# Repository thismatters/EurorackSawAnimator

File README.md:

# Saw Animator

```
     |\
<--> | \ | <-->
        \|
```

The Saw Animator combines a signal from an LFO with a saw audio signal to produce interesting overtones. In effect the LFO modulates the frequency of the saw wave causing the waveform to dance side-to-side on the oscilloscope. This module has an LFO of its own with adjustable rate, this can be overridden with a different CV signal.

The circuit here is based on the [Yusynth Saw Animator](https://yusynth.net/Modular/EN/SAWANIM/index.html) with minor tweaks to make it more Eurorack friendly. The changes I've made are thus:
* Selected resistors appropriate for +/-12V rails,
* Added polarity protection so that a backward power header doesn't fry anything (twin series schotty diodes: BAT54SL),
* Full surface mount design.

The Yusynth page is a treasure trove of information about this circuit that I am too amateur to claim as my own; please read that outstanding page before using this circuit. The page provides many details and other implementations of this circuit that you may find suitable.

The KiCAD project here uses the library/footprints [found in my companion repo](https://github.com/thismatters/EurorackKiCAD).

## Width

10hp on an Intellijel 1U rack.

## Inputs

Single potentiometer for adjusting LFO rate. Input jack for control voltage which overrides the LFO. Input jack for saw audio signal.

## Outputs

Output jack for animated saw output. LED which tracks the internal LFO.

## Adjustment

### Refine shape

- Ground the LFO input
- Connect a balanced saw wave (+/-5V) to the input
- Connect oscilloscope to the output
- Adjust RV2 (the one in the middle layer) until the triangle looks smooth

###  Set Balance

- Adjust RV1 so that the output is blanaced in the +/-5V range.

## Vendors

There are part numbers in the [BOM](saw-animator.csv) for many of the parts (not for basic passives though) at the following vendors:

* [Mouser](https://www.mouser.com): Needs no introduction. Get your ICs from here (or [digikey](https://www.digikey.com)).
* [Tayda Electronics](https://www.taydaelectronics.com/): Good supplier for passive components; audio jacks, and potentiometers. Their audio jacks are slightly smaller than the thonkiconn from thonk.
* [Love My Switches](https://lovemyswitches.com/): Has [really good knobs](https://lovemyswitches.com/anodized-aluminum-knob-the-lo-fi-1-4-smooth-shaft-12-5mm-od/) to go on those potentiometers!
* [OSHPark](https://oshpark.com/): Fast and (relatively) cheap PCB manufacturer. [V0 PCB](https://oshpark.com/shared_projects/MXBVaxpS)

## Issues

### V0
- The output saw waveshape is slightly distorted at the bottom, the slope is a little off
- Assembly was harder than necessary because the two boards with SMD components did not have enough support tabs to keep them together; each board had to be registered for solder paste application separately.

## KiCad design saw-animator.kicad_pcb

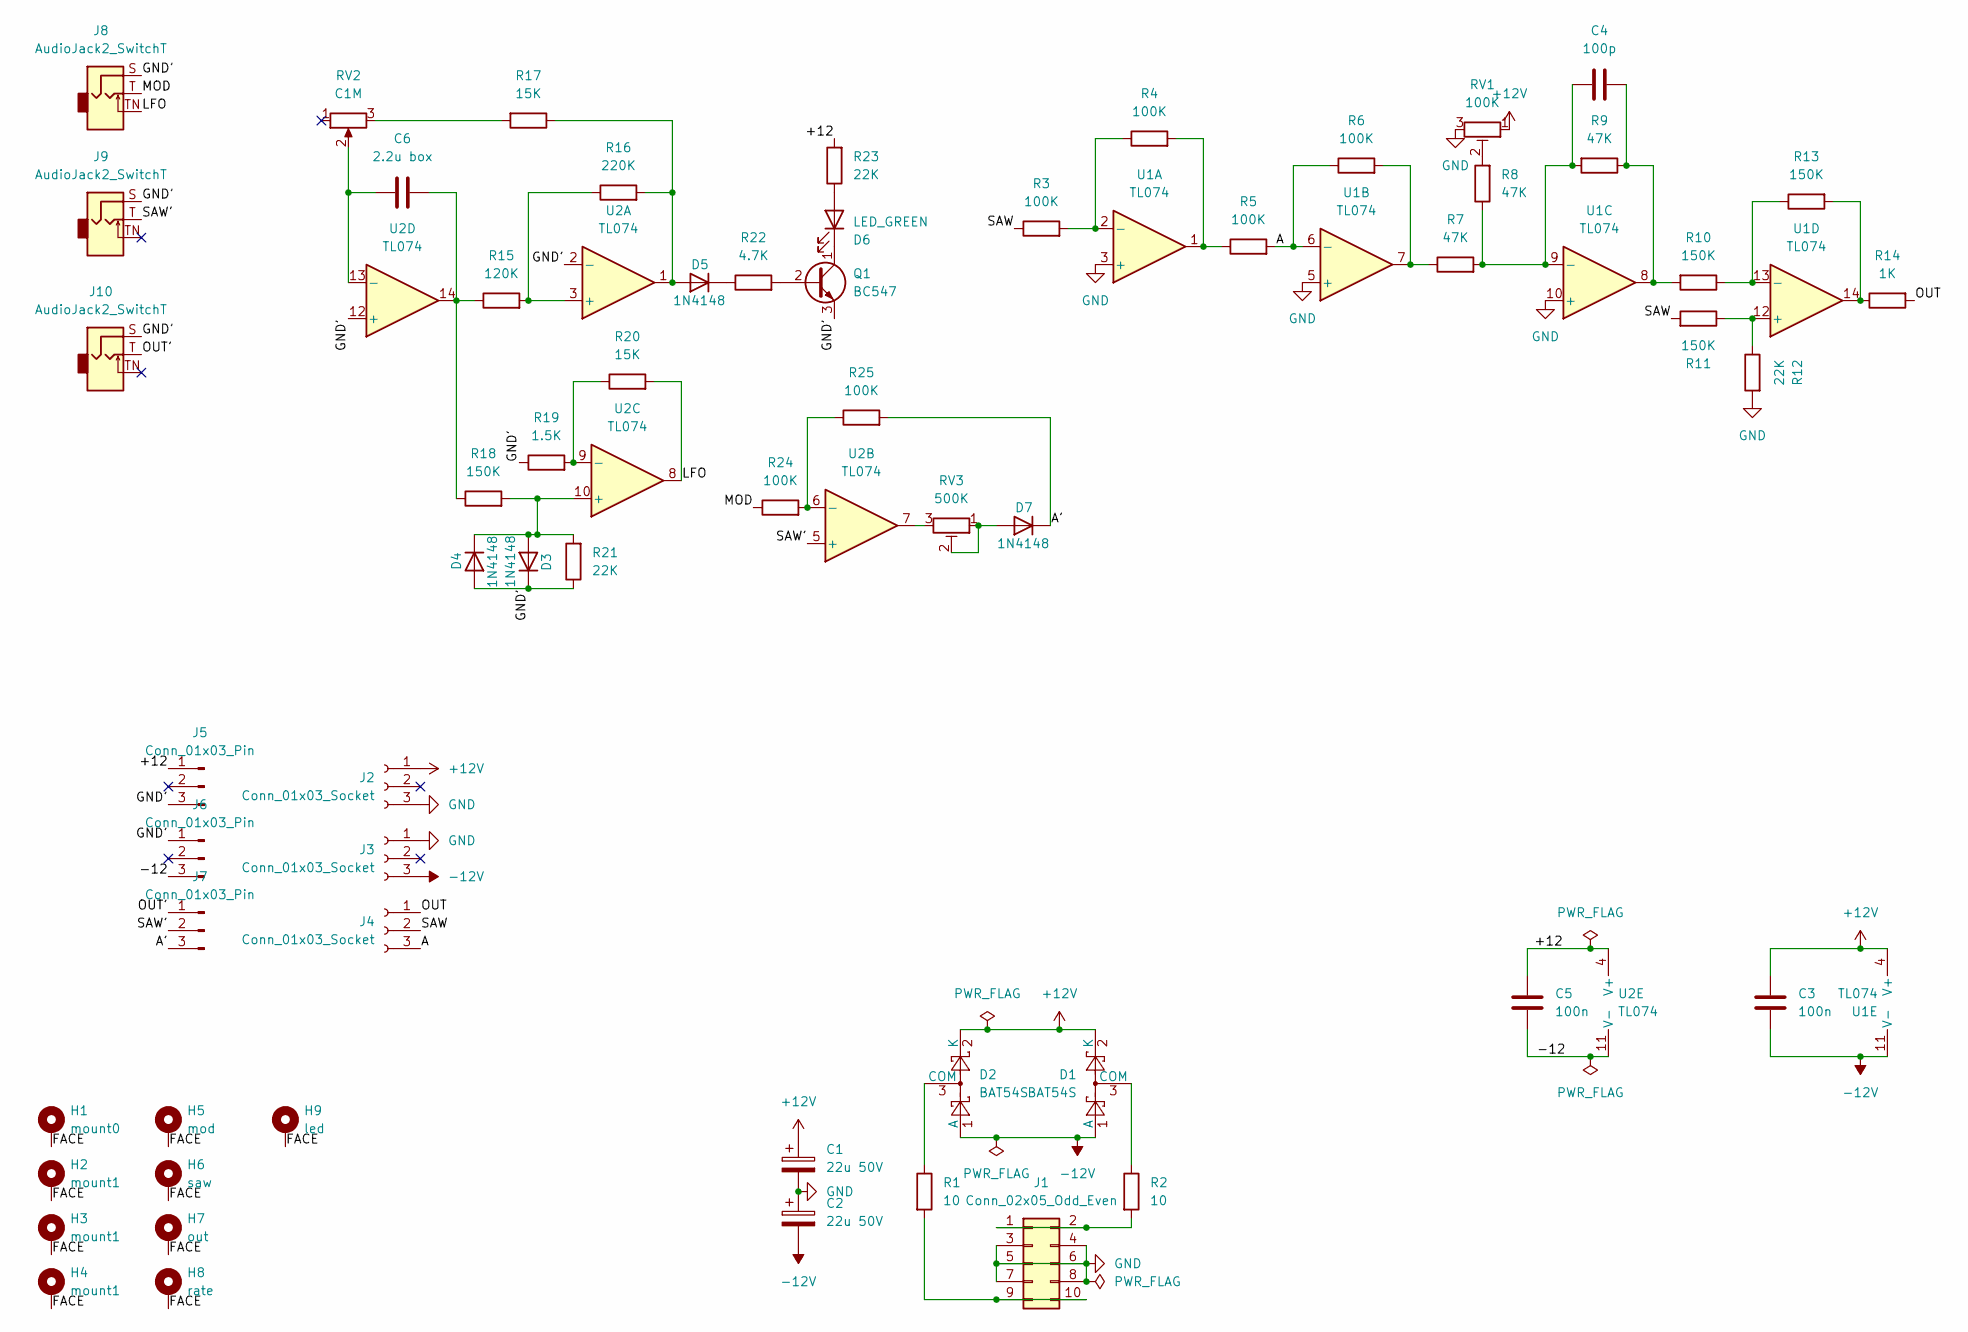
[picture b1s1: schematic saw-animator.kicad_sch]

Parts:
C1, C2: 22u 50V; CP_Radial_D5.0mm_P2.50mm
C3, C5: 100n; C_0805_2012Metric
C4: 100p; C_0805_2012Metric
C6: 2.2u box; C_Rect_L7.2mm_W7.2mm_P5.00mm_FKS2_FKP2_MKS2_MKP2
D1, D2: BAT54S; SOT-23; PartNum 863-BAT54SLT1G
D3, D4, D5, D7: 1N4148; D_SOD-323_HandSoldering
D6: LED_GREEN; LED_D3.0mm
H1: mount0; Mech-MountingHole
H2, H3, H4: mount1; Mech-MountingHole
H5: mod; Mech-AudioJack-Hole-Input-CV
H6: saw; Mech-AudioJack-Hole-Input
H7: out; Mech-AudioJack-Hole-Output
H8: rate; Mech-Potentiometer-Hole_level_90deg
H9: led; Mech-LED-Hole-3mm-Bezel
J1: Conn_02x05_Odd_Even; PinHeader_2x05_P2.54mm_Vertical; PartNum A-2939
J2, J3, J4: Conn_01x03_Socket; PinSocket_1x03_P2.54mm_Vertical
J5, J6, J7: Conn_01x03_Pin; PinHeader_1x03_P2.54mm_Vertical
J8, J9, J10: AudioJack2_SwitchT; AudioJack2_Tayda_A-2566; PartNum A-2566
Q1: BC547; TO-92_Inline_Wide; PartNum 637-BC547C
R1, R2: 10; R_0805_2012Metric
R3, R4, R5, R6, R24, R25: 100K; R_0805_2012Metric
R7, R8, R9: 47K; R_0805_2012Metric
R10, R11, R13, R18: 150K; R_0805_2012Metric
R12, R21, R23: 22K; R_0805_2012Metric
R14: 1K; R_0805_2012Metric
R15: 120K; R_0805_2012Metric
R16: 220K; R_0805_2012Metric
R17, R20: 15K; R_0805_2012Metric
R19: 1.5K; R_0805_2012Metric
R22: 4.7K; R_0805_2012Metric
RV1: 100K; Potentiometer_Bourns_3296W_Vertical
RV2: C1M; Potentiometer_RV16AF-41-15R1
RV3: 500K; Potentiometer_Bourns_3006P_Horizontal
U1, U2: TL074; SOIC-14_3.9x8.7mm_P1.27mm; PartNum 595-TL074CDR

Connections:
+12V: C1.1, C3.1, D1.2 (K), D2.2 (K), J2.1, RV1.1, U1.4 (V+)
-12V: C2.2, C3.2, D1.1 (A), D2.1 (A), J3.3, U1.11 (V-)
/+12: C5.1, J5.1, R23.2, U2.4 (V+)
/-12: C5.2, J6.3, U2.11 (V-)
/A: J4.3, R5.2, R6.1, U1.6 (-)
/A': D7.1 (K), J7.3, R25.2
/FACE: H1.1, H2.1, H3.1, H4.1, H5.1, H6.1, H7.1, H8.1, H9.1
/GND': D3.1 (K), D4.2 (A), J5.3, J6.1, J8.S, J9.S, J10.S, Q1.3 (E), R19.1, R21.1, U2.2 (-), U2.12 (+)
/LFO: J8.TN, R20.2, U2.8
/MOD: J8.T, R24.1
/OUT: J4.1, R14.2
/OUT': J7.1, J10.T
/SAW: J4.2, R3.1, R11.2
/SAW': J7.2, J9.T, U2.5 (+)
GND: C1.2, C2.1, J1.3, J1.4, J1.5, J1.6, J1.7, J1.8, J2.3, J3.1, R12.2, RV1.3, U1.3 (+), U1.5 (+), U1.10 (+)
unnamed: C4.2, R9.1, R10.2, U1.8
unnamed: C6.2, R15.1, R18.1, U2.14
unnamed: D1.3 (COM), R2.1
unnamed: D2.3 (COM), R1.1
unnamed: D3.2 (A), D4.1 (K), R18.2, R21.2, U2.10 (+)
unnamed: D5.2 (A), R16.2, R17.1, U2.1
unnamed: D5.1 (K), R22.1
unnamed: D6.2 (A), R23.1
unnamed: D6.1 (K), Q1.1 (C)
unnamed: D7.2 (A), RV3.1, RV3.2
unnamed: J1.1, J1.2, R2.2
unnamed: J1.9, J1.10, R1.2
unnamed: Q1.2 (B), R22.2
unnamed: R4.2, R5.1, U1.1
unnamed: R6.2, R7.1, U1.7
unnamed: R8.2, RV1.2
unnamed: R13.2, R14.1, U1.14
unnamed: R17.2, RV2.3
unnamed: RV3.3, U2.7
unnamed: R3.2, R4.1, U1.2 (-)
unnamed: C4.1, R7.2, R8.1, R9.2, U1.9 (-)
unnamed: R11.1, R12.1, U1.12 (+)
unnamed: R10.1, R13.1, U1.13 (-)
unnamed: R15.2, R16.1, U2.3 (+)
unnamed: R24.2, R25.1, U2.6 (-)
unnamed: R19.2, R20.1, U2.9 (-)
unnamed: C6.1, RV2.2, U2.13 (-)

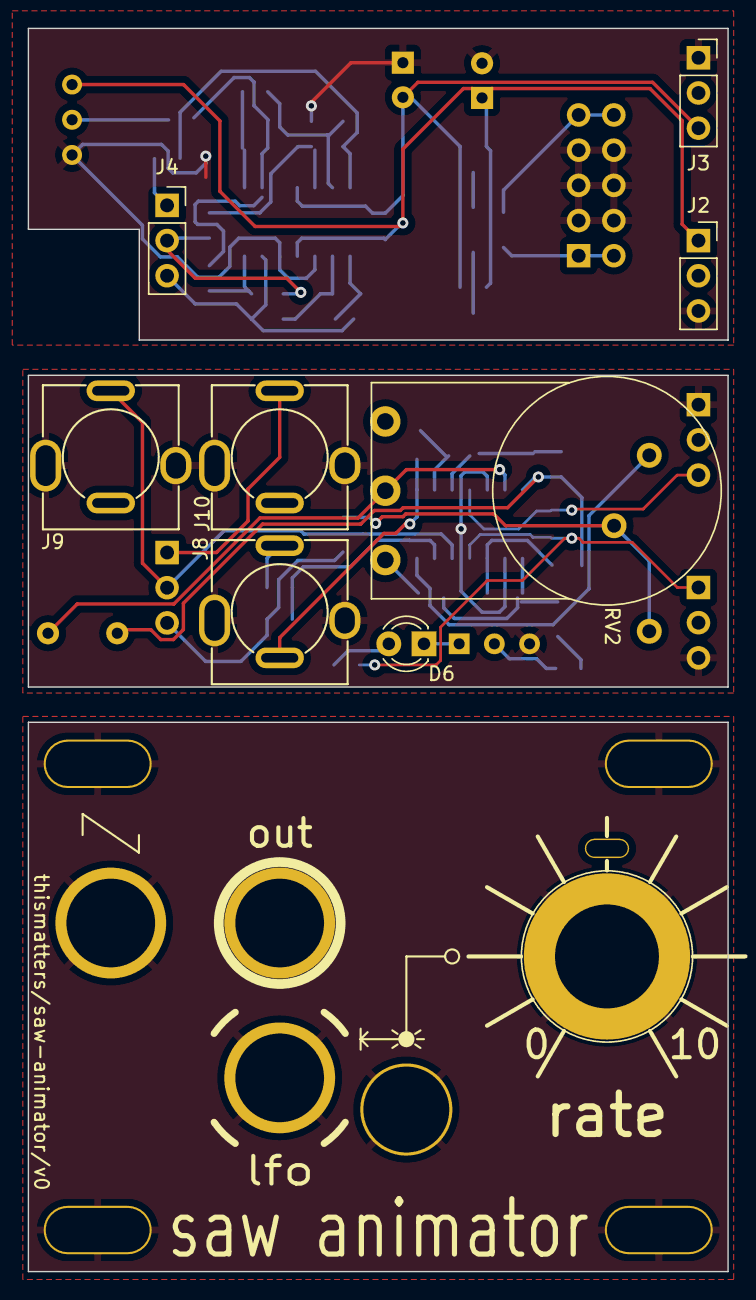
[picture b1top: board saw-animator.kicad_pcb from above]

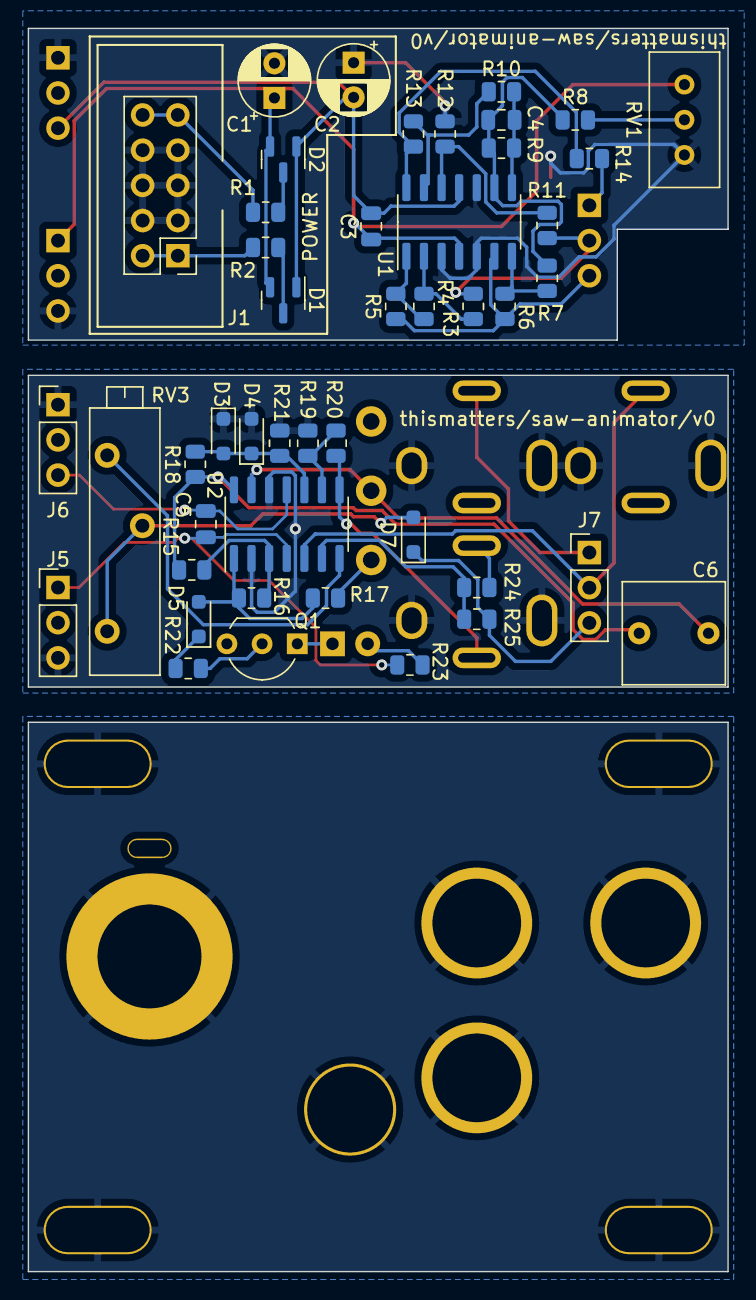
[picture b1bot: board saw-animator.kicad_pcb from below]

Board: 2 copper layers, 50.5 x 89.7 mm, 63 parts (46 on the bottom side), 42 nets.

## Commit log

2024-11-17 prototyped and tested ready for v0 manu
2024-11-24 fix: updating resistances to easily obtainable values
2024-12-29 seems good
